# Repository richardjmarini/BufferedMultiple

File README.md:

# BufferedMultiple
Circuit for a Modular Analog SynthesizerBuffered Multiple

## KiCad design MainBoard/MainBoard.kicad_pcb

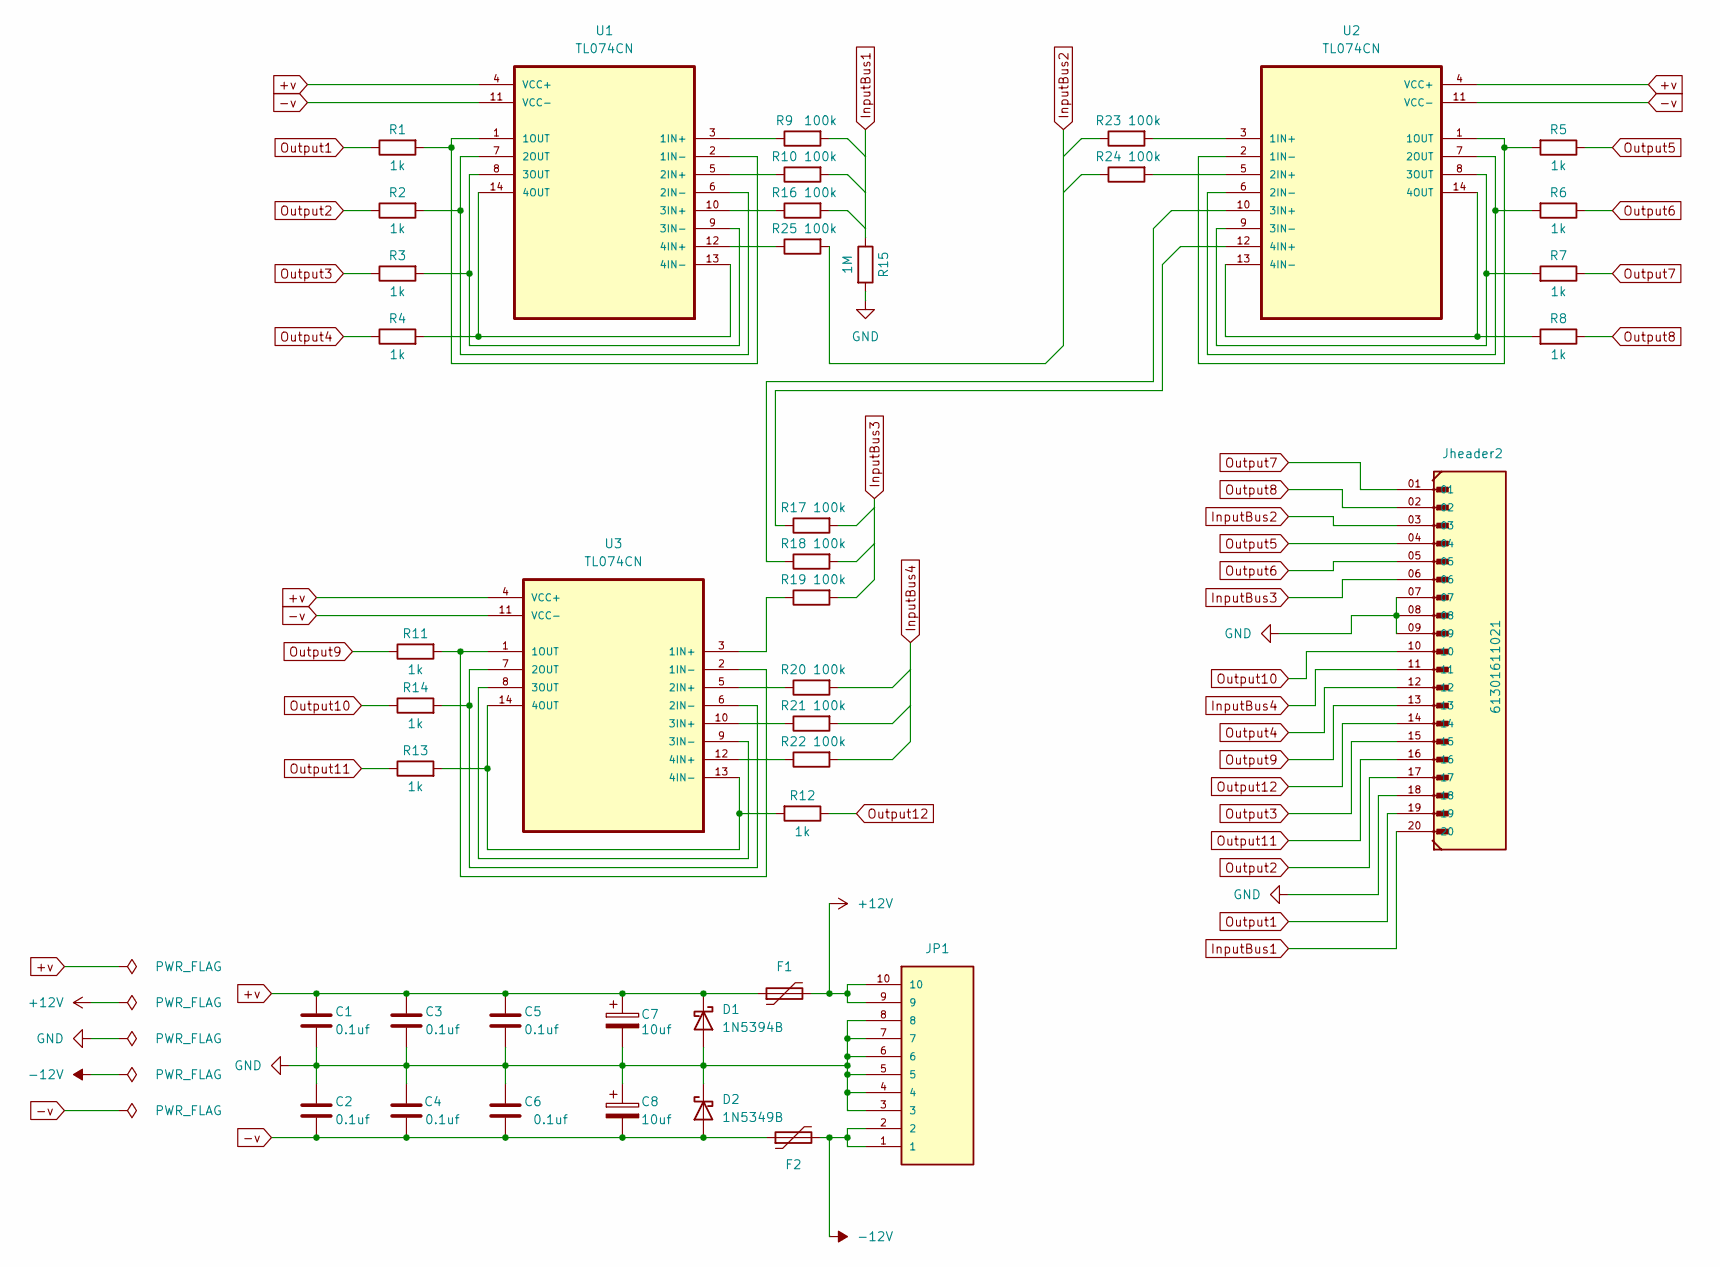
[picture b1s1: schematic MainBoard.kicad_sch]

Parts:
C1, C2, C3, C4, C5, C6: 0.1uf; C_Disc_D7.5mm_W4.4mm_P5.00mm
C7, C8: 10uf; CP_Radial_D5.0mm_P2.50mm
D1: 1N5394B; P2_DO-201
D2: 1N5349B; P2_DO-201
F1, F2: type="R" model="Polyfuse" lib=""; FUSRB510W81L1358T310H1980
JP1: 1761681-3; TE_1761681-3
Jheader2: 61301611021; AMPHENOL_75168-116-20LF; PARTREV AL
R1, R2, R3, R4, R5, R6, R7, R8, R11, R12, R13, R14: 1k; R_Axial_DIN0207_L6.3mm_D2.5mm_P10.16mm_Horizontal
R9, R10, R16, R17, R18, R19, R20, R21, R22, R23, R24, R25: 100k; R_Axial_DIN0207_L6.3mm_D2.5mm_P10.16mm_Horizontal
R15: 1M; R_Axial_DIN0207_L6.3mm_D2.5mm_P10.16mm_Horizontal
U1, U2, U3: TL074CN; DIP794W45P254L1969H508Q14

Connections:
+12V: F1.2, JP1.9, JP1.10
+v: C1.1, C3.1, C5.1, C7.1, D1.1 (K), F1.1, U1.4 (VCC+), U2.4 (VCC+), U3.4 (VCC+)
-12V: F2.2, JP1.1, JP1.2
-v: C2.1, C4.1, C6.1, C8.2, D2.2 (A), F2.1, U1.11 (VCC-), U2.11 (VCC-), U3.11 (VCC-)
GND: C1.2, C2.2, C3.2, C4.2, C5.2, C6.2, C7.2, C8.1, D1.2 (A), D2.1 (K), JP1.3, JP1.4, JP1.5, JP1.6, JP1.7, JP1.8, Jheader2.07, Jheader2.08, Jheader2.09, Jheader2.18, R15.2
InputBus1: Jheader2.20, R9.2, R10.2, R15.1, R16.2
InputBus2: Jheader2.03, R23.1, R24.1, R25.2
InputBus3: Jheader2.06, R17.2, R18.2, R19.2
InputBus4: Jheader2.11, R20.2, R21.2, R22.2
unnamed: R9.1, U1.3 (1IN+)
unnamed: R1.2, U1.1 (1OUT), U1.2 (1IN-)
unnamed: R10.1, U1.5 (2IN+)
unnamed: R2.2, U1.6 (2IN-), U1.7 (2OUT)
unnamed: R16.1, U1.10 (3IN+)
unnamed: R3.2, U1.8 (3OUT), U1.9 (3IN-)
unnamed: R25.1, U1.12 (4IN+)
unnamed: R4.2, U1.13 (4IN-), U1.14 (4OUT)
unnamed: R23.2, U2.3 (1IN+)
unnamed: R5.2, U2.1 (1OUT), U2.2 (1IN-)
unnamed: R24.2, U2.5 (2IN+)
unnamed: R6.2, U2.6 (2IN-), U2.7 (2OUT)
unnamed: R18.1, U2.10 (3IN+)
unnamed: R7.2, U2.8 (3OUT), U2.9 (3IN-)
unnamed: R17.1, U2.12 (4IN+)
unnamed: R8.2, U2.13 (4IN-), U2.14 (4OUT)
unnamed: R19.1, U3.3 (1IN+)
unnamed: R11.2, U3.1 (1OUT), U3.2 (1IN-)
unnamed: R20.1, U3.5 (2IN+)
unnamed: R14.2, U3.6 (2IN-), U3.7 (2OUT)
unnamed: R21.1, U3.10 (3IN+)
unnamed: U3.8 (3OUT), U3.9 (3IN-)
unnamed: R22.1, U3.12 (4IN+)
unnamed: R12.2, R13.2, U3.13 (4IN-), U3.14 (4OUT)
Output1: Jheader2.19, R1.1
Output2: Jheader2.17, R2.1
Output3: Jheader2.15, R3.1
Output4: Jheader2.12, R4.1
Output5: Jheader2.04, R5.1
Output6: Jheader2.05, R6.1
Output7: Jheader2.01, R7.1
Output8: Jheader2.02, R8.1
Output9: Jheader2.13, R11.1
Output10: Jheader2.10, R14.1
Output11: Jheader2.16, R13.1
Output12: Jheader2.14, R12.1

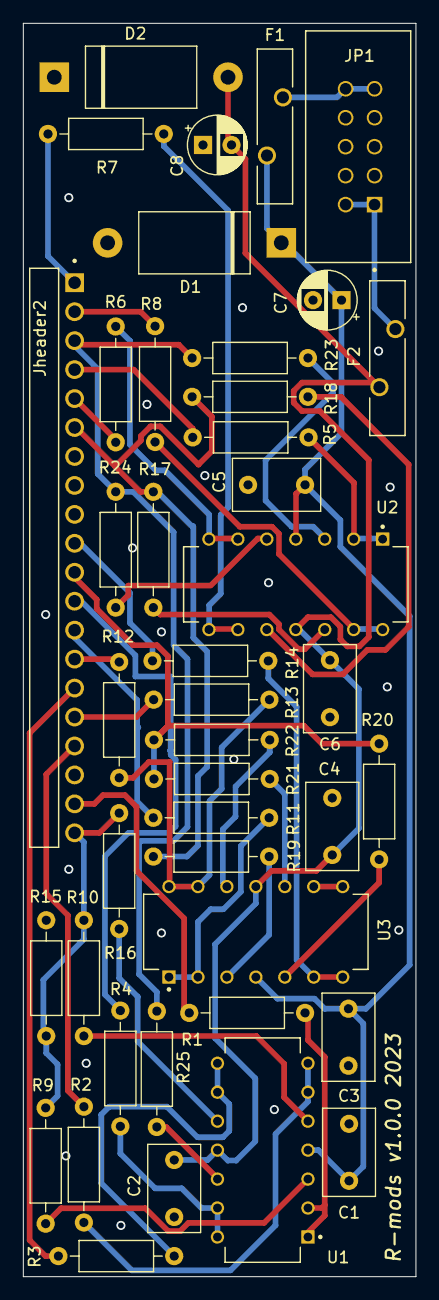
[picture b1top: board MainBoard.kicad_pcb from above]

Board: 4 copper layers, 34.4 x 110.0 mm, 42 parts (0 on the bottom side), 45 nets.

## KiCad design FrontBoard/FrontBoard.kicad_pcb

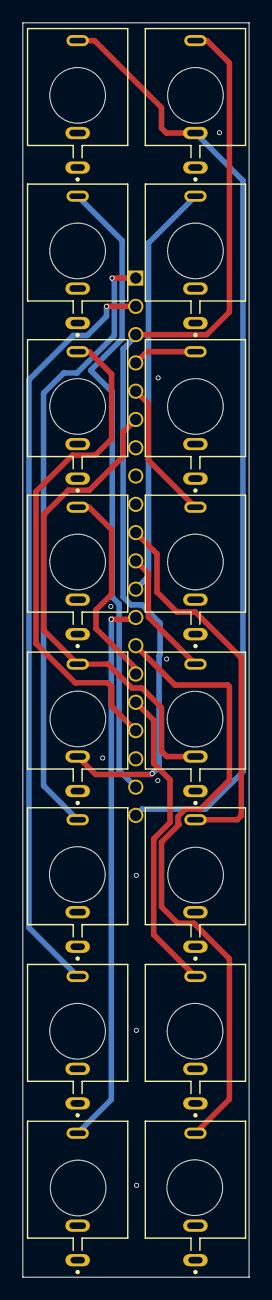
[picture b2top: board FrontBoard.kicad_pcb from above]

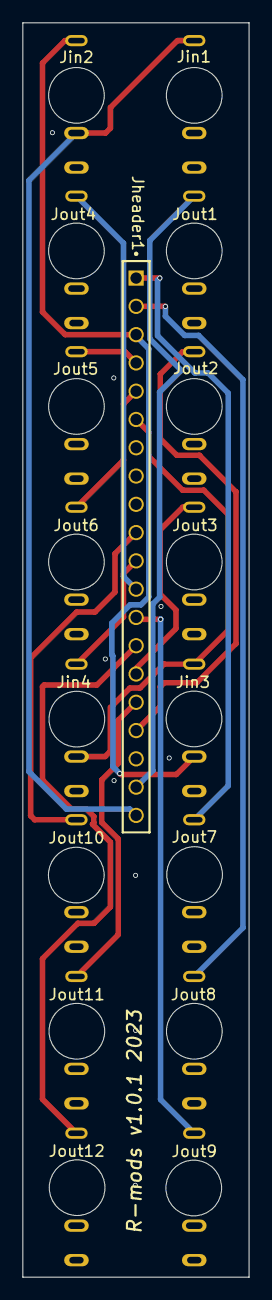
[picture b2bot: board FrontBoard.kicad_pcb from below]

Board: 4 copper layers, 20.3 x 112.7 mm, 33 parts (17 on the bottom side), 17 nets.

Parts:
Jheader1: 2-826646-0; SAMTEC_ESQ-120-12-T-S
Jin1, Jin2, Jin3, Jin4: PJ398SM-12; THONK_PJ398SM-12
Jinhole1, Jinhole2, Jinhole3, Jinhole4: MountingHole_5mm
Jout1, Jout2, Jout3, Jout4, Jout5, Jout6, Jout7, Jout8, Jout9, Jout10, Jout11, Jout12: PJ398SM-12; THONK_PJ398SM-12
Jouthole1, Jouthole3, Jouthole4, Jouthole5, Jouthole7, Jouthole9, Jouthole11: MountingHole_5mm
jouthole2, jouthole6, jouthole8, jouthole10, jouthole12: MountingHole_5mm

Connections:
GND: Jheader1.07, Jheader1.08, Jheader1.09, Jheader1.18, Jin1.1, Jin1.2, Jin2.1, Jin3.1, Jin4.1, Jout1.1, Jout1.2, Jout2.1, Jout2.2, Jout3.1, Jout3.2, Jout4.1, Jout4.2, Jout5.1, Jout5.2, Jout6.1, Jout6.2, Jout7.1, Jout7.2, Jout8.1, Jout8.2, Jout9.1, Jout9.2, Jout10.1, Jout10.2, Jout11.1, Jout11.2, Jout12.1, Jout12.2
InputBus1: Jheader1.20, Jin1.3, Jin2.2
InputBus2: Jheader1.03, Jin2.3, Jin3.2
InputBus3: Jheader1.06, Jin3.3, Jin4.2
InputBus4: Jheader1.11, Jin4.3
Output1: Jheader1.19, Jout1.3
Output2: Jheader1.17, Jout2.3
Output3: Jheader1.15, Jout3.3
Output4: Jheader1.12, Jout4.3
Output5: Jheader1.04, Jout5.3
Output6: Jheader1.05, Jout6.3
Output7: Jheader1.01, Jout7.3
Output8: Jheader1.02, Jout8.3
Output9: Jheader1.13, Jout9.3
Output10: Jheader1.10, Jout10.3
Output11: Jheader1.16, Jout11.3
Output12: Jheader1.14, Jout12.3

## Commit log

2023-04-05 added swap files to .gitignore
2023-04-05 updates simulation parameters
2023-04-05 added local models
2023-04-06 offset sin stimulus by -1.5v with a 3v peak to peak
2023-04-07 added additional output plots for first mult
2023-04-12 added 1M shunt on 1st input so op-amp inputs aren't floating when no signal is plugged in. Added 100k input resistors to each input. Updated ground to standard GND symbol. Added plot diretory to stor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
2023-06-02 updated power supply
2023-06-20 remove simulation. added project level symbols and footprints
2023-06-23 updated with new footprints and 3d models
2023-06-23 updated placements
2023-06-23 updated hardcoded paths
2023-06-24 updated placement
2023-06-27 first pass at routing mainboard
2023-06-28 added ground plane
2023-07-06 some updates
2023-07-06 updated board design rule constraints
2023-07-07 removed ground loops
2023-07-17 converted MainBoard to 4 layer stackup
2023-08-14 WIP: added faceplate
2023-08-15 WIP: faceplate design
2023-08-22 sent to production v1.0.0
2023-09-19 fixed incorrect routing on Jheader1, moved silk screens to back layer for easy readability after assembly, oriented all jacks in the upright postition to solvealignnment descrepency in 3d model vs ge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
2023-10-09 Passed Test. Production.
